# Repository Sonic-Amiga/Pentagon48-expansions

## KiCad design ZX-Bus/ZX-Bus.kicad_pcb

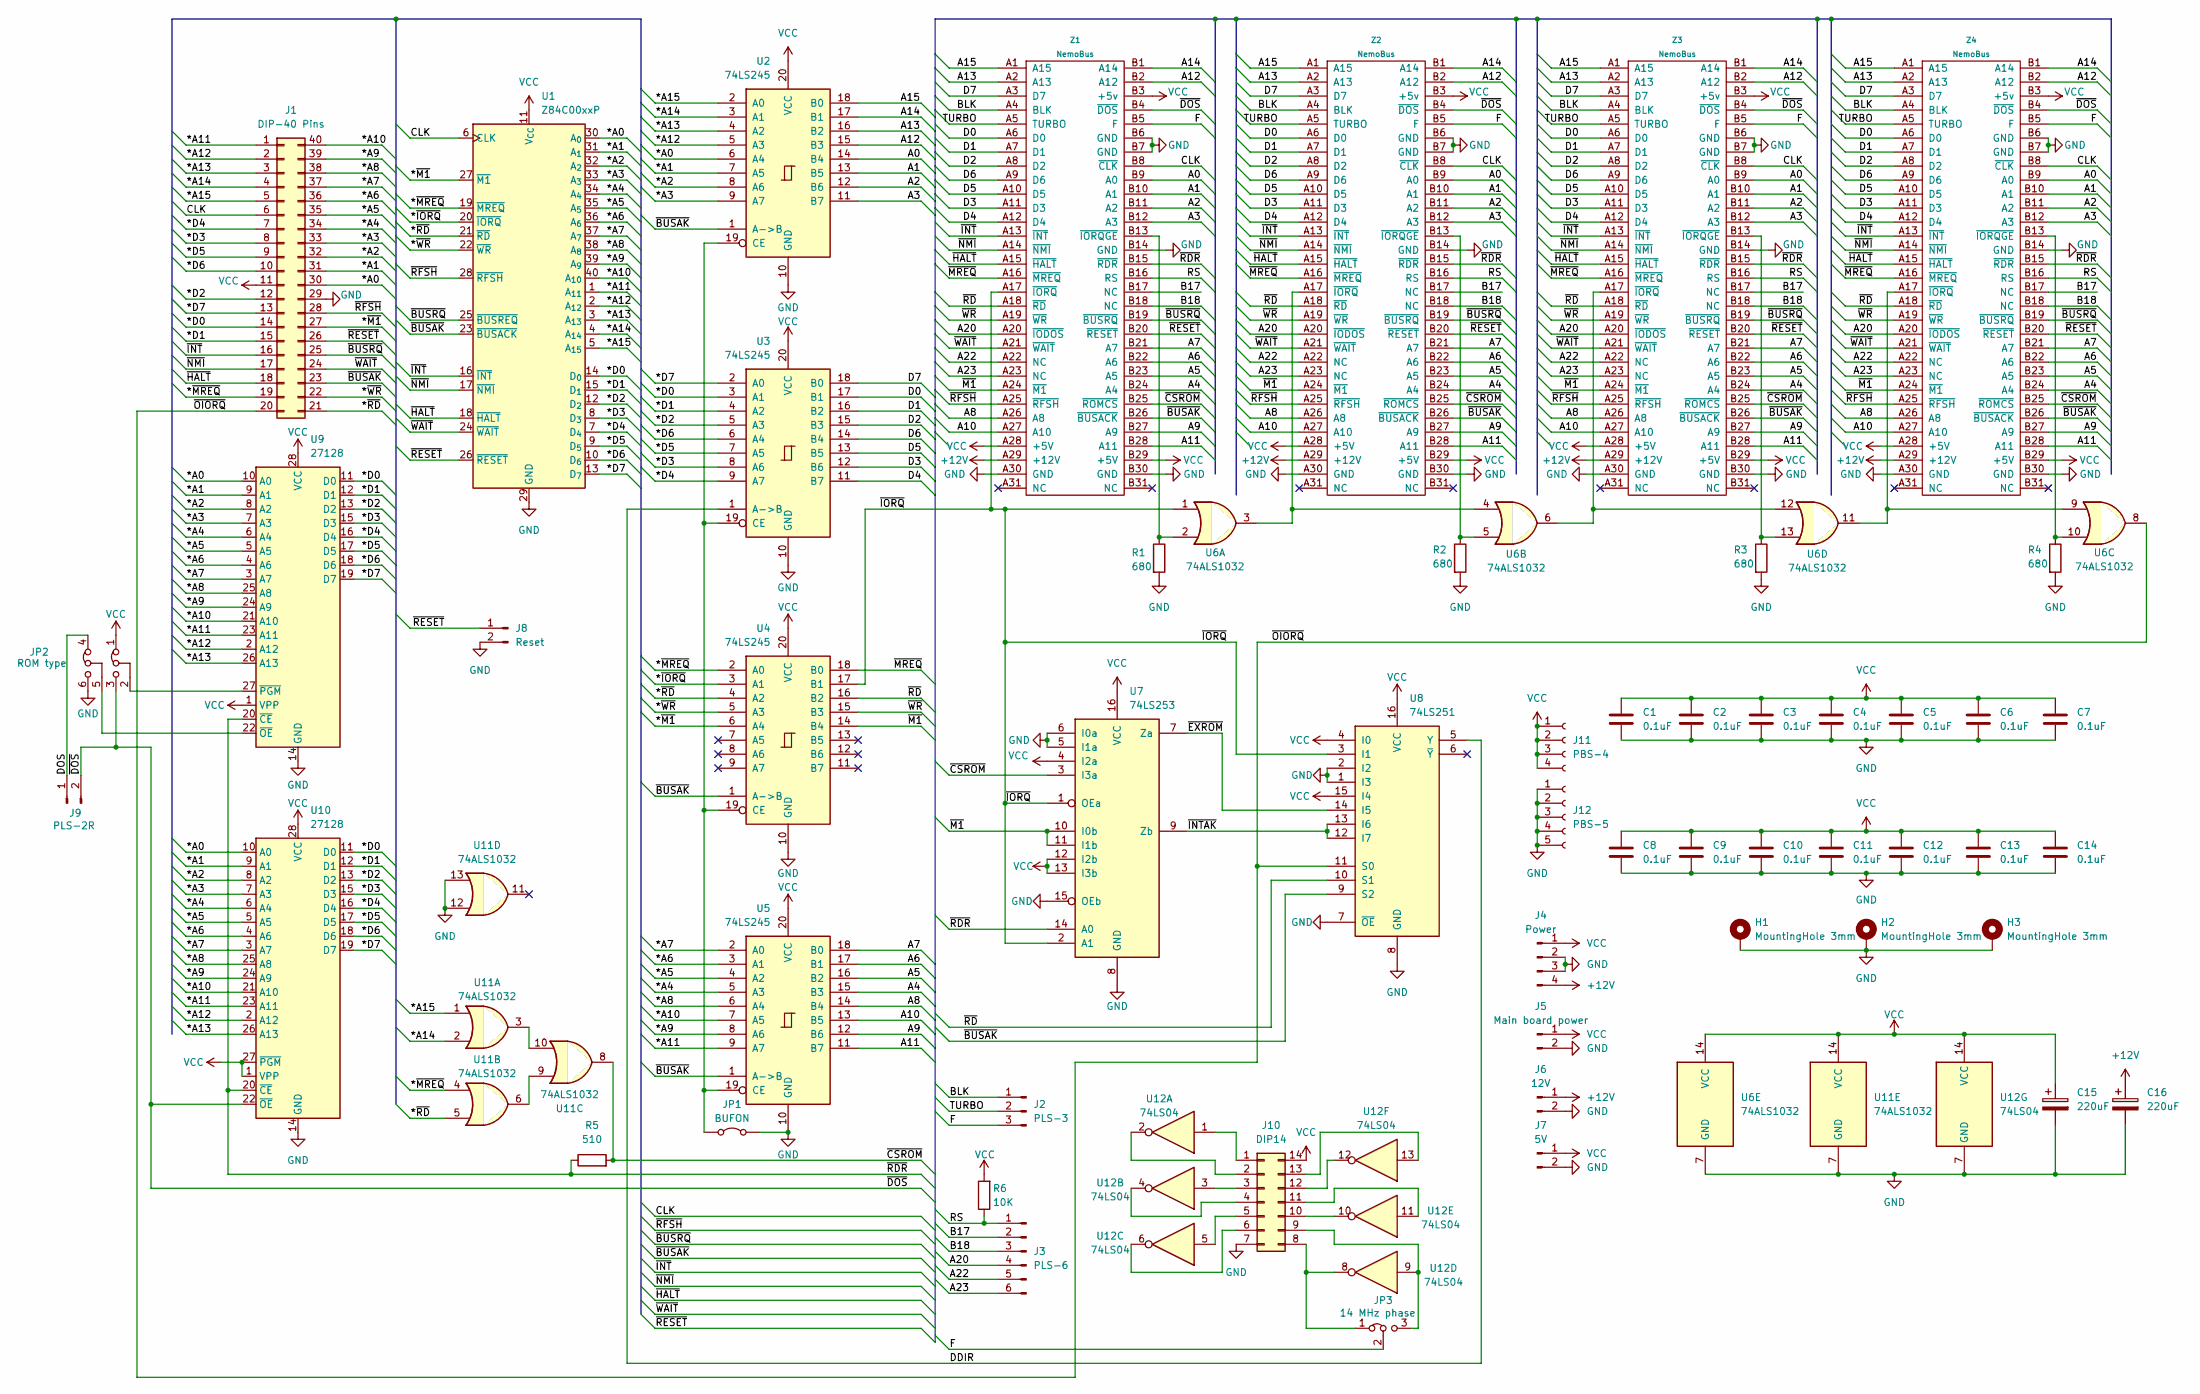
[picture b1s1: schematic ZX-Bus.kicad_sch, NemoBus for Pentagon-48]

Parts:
C1, C2, C3, C4, C5, C6, C7, C8, C9, C10, C11, C12, C13, C14: 0.1uF; C_Disc_D4.3mm_W1.9mm_P5.00mm
C15, C16: 220uF; CP_Radial_D5.0mm_P2.50mm
H1, H2, H3: MountingHole 3mm; MountingHole_3mm_Pad
J1: DIP-40 Pins; DIP40
J2: PLS-3; PinHeader_1x03_P2.54mm_Vertical
J3: PLS-6; PinHeader_1x06_P2.54mm_Vertical
J4: Power; PhoenixContact_MSTBA_2,5_4-G-5,08_1x04_P5.08mm_Horizontal
J5: Main board power; PhoenixContact_MC_1,5_2-G-5.08_1x02_P5.08mm_Horizontal
J6: 12V; JST_XH_S2B-XH-A-1_1x02_P2.50mm_Horizontal
J7: 5V; JST_XH_S2B-XH-A-1_1x02_P2.50mm_Horizontal
J8: Reset; PinHeader_1x02_P2.54mm_Vertical
J9: PLS-2R; PinHeader_1x02_P2.54mm_Horizontal
J10: DIP14; DIP-14_W7.62mm-Pins
J11: PBS-4; PinSocket_1x04_P2.54mm_Vertical
J12: PBS-5; PinSocket_1x05_P2.54mm_Vertical
JP1: BUFON; TestPoint_2Pads_Pitch2.54mm_Drill0.8mm
JP2: ROM type; PinHeader_3x02_P2.54mm_Vertical
JP3: 14 MHz phase; PinHeader_1x03_P2.54mm_Vertical
R1, R2, R3, R4: 680; R_Axial_DIN0207_L6.3mm_D2.5mm_P10.16mm_Horizontal
R5: 510; R_Axial_DIN0207_L6.3mm_D2.5mm_P10.16mm_Horizontal
R6: 10K; R_Axial_DIN0207_L6.3mm_D2.5mm_P10.16mm_Horizontal
U1: Z84C00xxP; DIP-40_W15.24mm_Socket
U2, U3, U4, U5: 74LS245; DIP-20_W7.62mm
U6, U11: 74ALS1032; DIP-14_W7.62mm
U7: 74LS253; DIP-16_W7.62mm
U8: 74LS251; DIP-16_W7.62mm
U9, U10: 27128; DIP-28_W15.24mm_Socket
U12: 74LS04; DIP-14_W7.62mm_Socket
Z1, Z2, Z3, Z4: NemoBus; NemoBus_SL62_Slot

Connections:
+12V: C16.1, J4.4, J6.1, Z1.A29 (+12V), Z2.A29 (+12V), Z3.A29 (+12V), Z4.A29 (+12V)
/*A0: J1.30, U1.30 (A_{0}), U2.6 (A4), U9.10 (A0), U10.10 (A0)
/*A1: J1.31, U1.31 (A_{1}), U2.7 (A5), U9.9 (A1), U10.9 (A1)
/*A2: J1.32, U1.32 (A_{2}), U2.8 (A6), U9.8 (A2), U10.8 (A2)
/*A3: J1.33, U1.33 (A_{3}), U2.9 (A7), U9.7 (A3), U10.7 (A3)
/*A4: J1.34, U1.34 (A_{4}), U5.5 (A3), U9.6 (A4), U10.6 (A4)
/*A5: J1.35, U1.35 (A_{5}), U5.4 (A2), U9.5 (A5), U10.5 (A5)
/*A6: J1.36, U1.36 (A_{6}), U5.3 (A1), U9.4 (A6), U10.4 (A6)
/*A7: J1.37, U1.37 (A_{7}), U5.2 (A0), U9.3 (A7), U10.3 (A7)
/*A8: J1.38, U1.38 (A_{8}), U5.6 (A4), U9.25 (A8), U10.25 (A8)
/*A9: J1.39, U1.39 (A_{9}), U5.8 (A6), U9.24 (A9), U10.24 (A9)
/*A10: J1.40, U1.40 (A_{10}), U5.7 (A5), U9.21 (A10), U10.21 (A10)
/*A11: J1.1, U1.1 (A_{11}), U5.9 (A7), U9.23 (A11), U10.23 (A11)
/*A12: J1.2, U1.2 (A_{12}), U2.5 (A3), U9.2 (A12), U10.2 (A12)
/*A13: J1.3, U1.3 (A_{13}), U2.4 (A2), U9.26 (A13), U10.26 (A13)
/*A14: J1.4, U1.4 (A_{14}), U2.3 (A1), U11.2
/*A15: J1.5, U1.5 (A_{15}), U2.2 (A0), U11.1
/*D0: J1.14, U1.14 (D_{0}), U3.3 (A1), U9.11 (D0), U10.11 (D0)
/*D1: J1.15, U1.15 (D_{1}), U3.4 (A2), U9.12 (D1), U10.12 (D1)
/*D2: J1.12, U1.12 (D_{2}), U3.5 (A3), U9.13 (D2), U10.13 (D2)
/*D3: J1.8, U1.8 (D_{3}), U3.8 (A6), U9.15 (D3), U10.15 (D3)
/*D4: J1.7, U1.7 (D_{4}), U3.9 (A7), U9.16 (D4), U10.16 (D4)
/*D5: J1.9, U1.9 (D_{5}), U3.7 (A5), U9.17 (D5), U10.17 (D5)
/*D6: J1.10, U1.10 (D_{6}), U3.6 (A4), U9.18 (D6), U10.18 (D6)
/*D7: J1.13, U1.13 (D_{7}), U3.2 (A0), U9.19 (D7), U10.19 (D7)
/*~IORQ: U1.20 (~IORQ), U4.3 (A1)
/*~M1: J1.27, U1.27 (~M1), U4.6 (A4)
/*~MREQ: J1.19, U1.19 (~MREQ), U4.2 (A0), U11.4
/*~RD: J1.21, U1.21 (~RD), U4.4 (A2), U11.5
/*~WR: J1.22, U1.22 (~WR), U4.5 (A3)
/A0: U2.14 (B4), Z1.B9 (A0), Z2.B9 (A0), Z3.B9 (A0), Z4.B9 (A0)
/A1: U2.13 (B5), Z1.B10 (A1), Z2.B10 (A1), Z3.B10 (A1), Z4.B10 (A1)
/A2: U2.12 (B6), Z1.B11 (A2), Z2.B11 (A2), Z3.B11 (A2), Z4.B11 (A2)
/A3: U2.11 (B7), Z1.B12 (A3), Z2.B12 (A3), Z3.B12 (A3), Z4.B12 (A3)
/A4: U5.15 (B3), Z1.B24 (A4), Z2.B24 (A4), Z3.B24 (A4), Z4.B24 (A4)
/A5: U5.16 (B2), Z1.B23 (A5), Z2.B23 (A5), Z3.B23 (A5), Z4.B23 (A5)
/A6: U5.17 (B1), Z1.B22 (A6), Z2.B22 (A6), Z3.B22 (A6), Z4.B22 (A6)
/A7: U5.18 (B0), Z1.B21 (A7), Z2.B21 (A7), Z3.B21 (A7), Z4.B21 (A7)
/A8: U5.14 (B4), Z1.A26 (A8), Z2.A26 (A8), Z3.A26 (A8), Z4.A26 (A8)
/A9: U5.12 (B6), Z1.B27 (A9), Z2.B27 (A9), Z3.B27 (A9), Z4.B27 (A9)
/A10: U5.13 (B5), Z1.A27 (A10), Z2.A27 (A10), Z3.A27 (A10), Z4.A27 (A10)
/A11: U5.11 (B7), Z1.B28 (A11), Z2.B28 (A11), Z3.B28 (A11), Z4.B28 (A11)
/A12: U2.15 (B3), Z1.B2 (A12), Z2.B2 (A12), Z3.B2 (A12), Z4.B2 (A12)
/A13: U2.16 (B2), Z1.A2 (A13), Z2.A2 (A13), Z3.A2 (A13), Z4.A2 (A13)
/A14: U2.17 (B1), Z1.B1 (A14), Z2.B1 (A14), Z3.B1 (A14), Z4.B1 (A14)
/A15: U2.18 (B0), Z1.A1 (A15), Z2.A1 (A15), Z3.A1 (A15), Z4.A1 (A15)
/A20: J3.4, Z1.A20 (~IODOS), Z2.A20 (~IODOS), Z3.A20 (~IODOS), Z4.A20 (~IODOS)
/A22: J3.5, Z1.A22 (NC), Z2.A22 (NC), Z3.A22 (NC), Z4.A22 (NC)
/A23: J3.6, Z1.A23 (NC), Z2.A23 (NC), Z3.A23 (NC), Z4.A23 (NC)
/B17: J3.2, Z1.B17 (NC), Z2.B17 (NC), Z3.B17 (NC), Z4.B17 (NC)
/B18: J3.3, Z1.B18 (NC), Z2.B18 (NC), Z3.B18 (NC), Z4.B18 (NC)
/BLK: J2.1, Z1.A4 (BLK), Z2.A4 (BLK), Z3.A4 (BLK), Z4.A4 (BLK)
/CLK: J1.6, U1.6 (CLK), Z1.B8 (~CLK), Z2.B8 (~CLK), Z3.B8 (~CLK), Z4.B8 (~CLK)
/D0: U3.17 (B1), Z1.A6 (D0), Z2.A6 (D0), Z3.A6 (D0), Z4.A6 (D0)
/D1: U3.16 (B2), Z1.A7 (D1), Z2.A7 (D1), Z3.A7 (D1), Z4.A7 (D1)
/D2: U3.15 (B3), Z1.A8 (D2), Z2.A8 (D2), Z3.A8 (D2), Z4.A8 (D2)
/D3: U3.12 (B6), Z1.A11 (D3), Z2.A11 (D3), Z3.A11 (D3), Z4.A11 (D3)
/D4: U3.11 (B7), Z1.A12 (D4), Z2.A12 (D4), Z3.A12 (D4), Z4.A12 (D4)
/D5: U3.13 (B5), Z1.A10 (D5), Z2.A10 (D5), Z3.A10 (D5), Z4.A10 (D5)
/D6: U3.14 (B4), Z1.A9 (D6), Z2.A9 (D6), Z3.A9 (D6), Z4.A9 (D6)
/D7: U3.18 (B0), Z1.A3 (D7), Z2.A3 (D7), Z3.A3 (D7), Z4.A3 (D7)
/DDIR: U3.1 (A->B), U8.5 (Y)
/DOS: J9.1, JP2.4 (A)
/F: J2.3, JP3.2 (C), Z1.B5 (F), Z2.B5 (F), Z3.B5 (F), Z4.B5 (F)
/RS: J3.1, R6.1, Z1.B16 (RS), Z2.B16 (RS), Z3.B16 (RS), Z4.B16 (RS)
/TURBO: J2.2, Z1.A5 (TURBO), Z2.A5 (TURBO), Z3.A5 (TURBO), Z4.A5 (TURBO)
/~BUSAK: J1.23, U1.23 (~BUSACK), U2.1 (A->B), U4.1 (A->B), U5.1 (A->B), U8.9 (S2), Z1.B26 (~BUSACK), Z2.B26 (~BUSACK), Z3.B26 (~BUSACK), Z4.B26 (~BUSACK)
/~BUSRQ: J1.25, U1.25 (~BUSREQ), Z1.B19 (~BUSRQ), Z2.B19 (~BUSRQ), Z3.B19 (~BUSRQ), Z4.B19 (~BUSRQ)
/~CSROM: R5.2, U7.3 (I3a), U11.8, Z1.B25 (~ROMCS), Z2.B25 (~ROMCS), Z3.B25 (~ROMCS), Z4.B25 (~ROMCS)
/~DOS: J9.2, JP2.3 (B), U10.22 (~OE), Z1.B4 (~DOS), Z2.B4 (~DOS), Z3.B4 (~DOS), Z4.B4 (~DOS)
/~EXROM: U7.7 (Za), U8.14 (I5)
/~HALT: J1.18, U1.18 (~HALT), Z1.A15 (~HALT), Z2.A15 (~HALT), Z3.A15 (~HALT), Z4.A15 (~HALT)
/~INTAK: U7.9 (Zb), U8.12 (I7), U8.13 (I6)
/~INT: J1.16, U1.16 (~INT), Z1.A13 (~INT), Z2.A13 (~INT), Z3.A13 (~INT), Z4.A13 (~INT)
/~IORQ: U4.17 (B1), U6.1, U7.1 (OEa), U7.2 (A1), U8.3 (I1), Z1.A17 (~IORQ)
/~M1: U4.14 (B4), U7.10 (I0b), U7.11 (I1b), Z1.A24 (~M1), Z2.A24 (~M1), Z3.A24 (~M1), Z4.A24 (~M1)
/~MREQ: U4.18 (B0), Z1.A16 (~MREQ), Z2.A16 (~MREQ), Z3.A16 (~MREQ), Z4.A16 (~MREQ)
/~NMI: J1.17, U1.17 (~NMI), Z1.A14 (~NMI), Z2.A14 (~NMI), Z3.A14 (~NMI), Z4.A14 (~NMI)
/~OIORQ: J1.20, U6.8, U8.11 (S0)
/~RDR: R5.1, U7.14 (A0), U9.20 (~CE), U10.20 (~CE), Z1.B15 (~RDR), Z2.B15 (~RDR), Z3.B15 (~RDR), Z4.B15 (~RDR)
/~RD: U4.16 (B2), U8.10 (S1), Z1.A18 (~RD), Z2.A18 (~RD), Z3.A18 (~RD), Z4.A18 (~RD)
/~RESET: J1.26, J8.1, U1.26 (~RESET), Z1.B20 (~RESET), Z2.B20 (~RESET), Z3.B20 (~RESET), Z4.B20 (~RESET)
/~RFSH: J1.28, U1.28 (~RFSH), Z1.A25 (~RFSH), Z2.A25 (~RFSH), Z3.A25 (~RFSH), Z4.A25 (~RFSH)
/~WAIT: J1.24, U1.24 (~WAIT), Z1.A21 (~WAIT), Z2.A21 (~WAIT), Z3.A21 (~WAIT), Z4.A21 (~WAIT)
/~WR: U4.15 (B3), Z1.A19 (~WR), Z2.A19 (~WR), Z3.A19 (~WR), Z4.A19 (~WR)
GND: C1.2, C2.2, C3.2, C4.2, C5.2, C6.2, C7.2, C8.2, C9.2, C10.2, C11.2, C12.2, C13.2, C14.2, C15.2, C16.2, H1.1 (1_1), H2.1 (1_1), H3.1 (1_1), J1.29, J4.2, J4.3, J5.2, J6.2, J7.2, J8.2, J10.7, J12.1, J12.2, J12.3, J12.4, J12.5, JP1.2 (B), JP2.6 (B), R1.2, R2.2, R3.2, R4.2, U1.29 (GND), U2.10 (GND), U3.10 (GND), U4.10 (GND), U5.10 (GND), U6.7 (GND), U7.5 (I1a), U7.6 (I0a), U7.8 (GND), U7.15 (OEb), U8.1 (I3), U8.2 (I2), U8.7 (~OE), U8.8 (GND), U9.14 (GND), U10.14 (GND), U11.7 (GND), U11.12, U11.13, U12.7 (GND), Z1.A30 (GND), Z1.B6 (GND), Z1.B7 (GND), Z1.B14 (GND), Z1.B30 (GND), Z2.A30 (GND), Z2.B6 (GND), Z2.B7 (GND), Z2.B14 (GND), Z2.B30 (GND), Z3.A30 (GND), Z3.B6 (GND), Z3.B7 (GND), Z3.B14 (GND), Z3.B30 (GND), Z4.A30 (GND), Z4.B6 (GND), Z4.B7 (GND), Z4.B14 (GND), Z4.B30 (GND)
unnamed: J10.1, U12.1
unnamed: J10.2, U12.2
unnamed: J10.3, U12.3
unnamed: J10.4, U12.4
unnamed: J10.5, U12.5
unnamed: J10.6, U12.6
unnamed: J10.8, JP3.1 (A), U12.8
unnamed: J10.9, JP3.3 (B), U12.9
unnamed: J10.10, U12.10
unnamed: J10.11, U12.11
unnamed: J10.12, U12.12
unnamed: J10.13, U12.13
unnamed: JP1.1 (A), U2.19 (CE), U3.19 (CE), U4.19 (CE), U5.19 (CE)
unnamed: JP2.5 (C), U9.22 (~OE)
unnamed: JP2.2 (C), U9.27 (~PGM)
unnamed: U11.6, U11.9
unnamed: U11.3, U11.10
unnamed: R1.1, U6.2, Z1.B13 (~IORQGE)
unnamed: R2.1, U6.5, Z2.B13 (~IORQGE)
unnamed: U6.3, U6.4, Z2.A17 (~IORQ)
unnamed: R3.1, U6.13, Z3.B13 (~IORQGE)
unnamed: U6.6, U6.12, Z3.A17 (~IORQ)
unnamed: R4.1, U6.10, Z4.B13 (~IORQGE)
unnamed: U6.9, U6.11, Z4.A17 (~IORQ)
VCC: C1.1, C2.1, C3.1, C4.1, C5.1, C6.1, C7.1, C8.1, C9.1, C10.1, C11.1, C12.1, C13.1, C14.1, C15.1, J1.11, J4.1, J5.1, J7.1, J10.14, J11.1, J11.2, J11.3, J11.4, JP2.1 (A), R6.2, U1.11 (V_{CC}), U2.20 (VCC), U3.20 (VCC), U4.20 (VCC), U5.20 (VCC), U6.14 (VCC), U7.4 (I2a), U7.12 (I2b), U7.13 (I3b), U7.16 (VCC), U8.4 (I0), U8.15 (I4), U8.16 (VCC), U9.1 (VPP), U9.28 (VCC), U10.1 (VPP), U10.27 (~PGM), U10.28 (VCC), U11.14 (VCC), U12.14 (VCC), Z1.A28 (+5V), Z1.B3 (+5v), Z1.B29 (+5V), Z2.A28 (+5V), Z2.B3 (+5v), Z2.B29 (+5V), Z3.A28 (+5V), Z3.B3 (+5v), Z3.B29 (+5V), Z4.A28 (+5V), Z4.B3 (+5v), Z4.B29 (+5V)

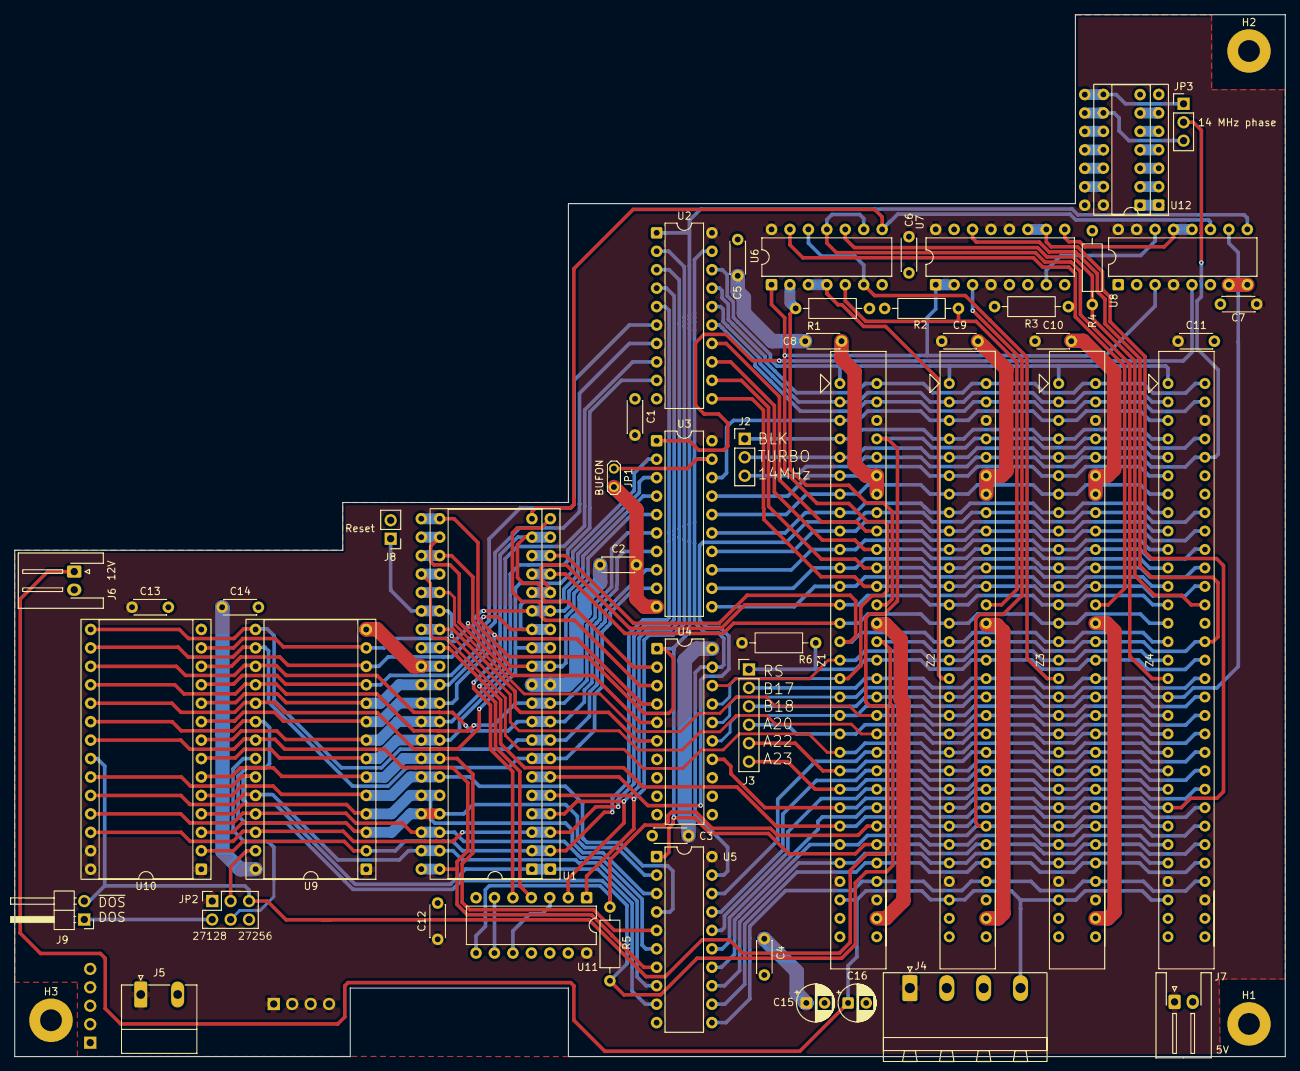
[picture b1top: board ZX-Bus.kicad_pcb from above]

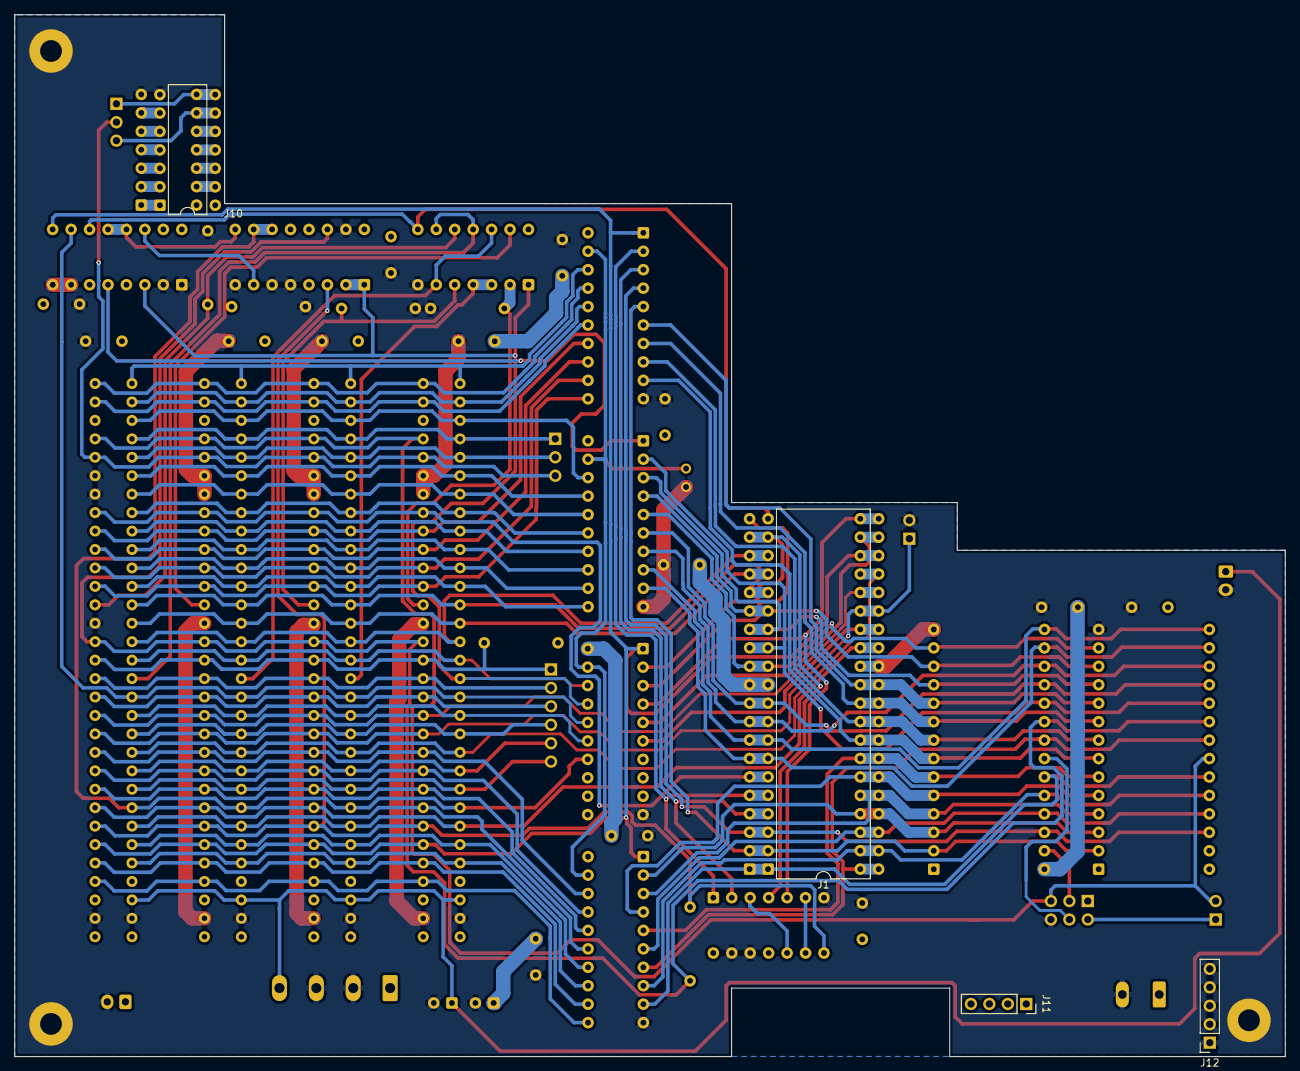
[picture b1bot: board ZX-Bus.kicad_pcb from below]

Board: 2 copper layers, 175.0 x 143.5 mm, 56 parts (2 on the bottom side), 111 nets.

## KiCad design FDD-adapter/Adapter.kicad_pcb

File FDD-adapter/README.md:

# Введение

Этот проект представляет собой переходник на стандартный интерфейс флоппи-дисковода
для ZX-Spectrum-совместимого компьютера "Пентагон-48". Для классических вариантов
платы, не имеющих буферизации линий выбора дисковода, предусмотрена возможность
установки буфера 74LS07. Если у вас есть этот буфер на плате, вы можете просто
замкнуть накоротко соответствующие дорожки.

# Рекомендации по сборке и подключению

Данный переходник использует 30-контактный разъём со стороны Пентагона, хотя на плате
компьютера посадочное место под разъём 32 контакта. Это сделано по двум соображениям.
Во-первых, стандартные разъёмы IDC имеются только под 30 контактов. Во-вторых, подача
питания через разъём дисковода на весь компьютер - не очень хорошая идея из-за тонких
дорожек. Поэтому я принял решение использовать 30-контактный разъём для данных и
отдельный 2-контактный разъём для подачи питания 12В. В качестве последнего хорошо
подходит разъём JST EHR-2

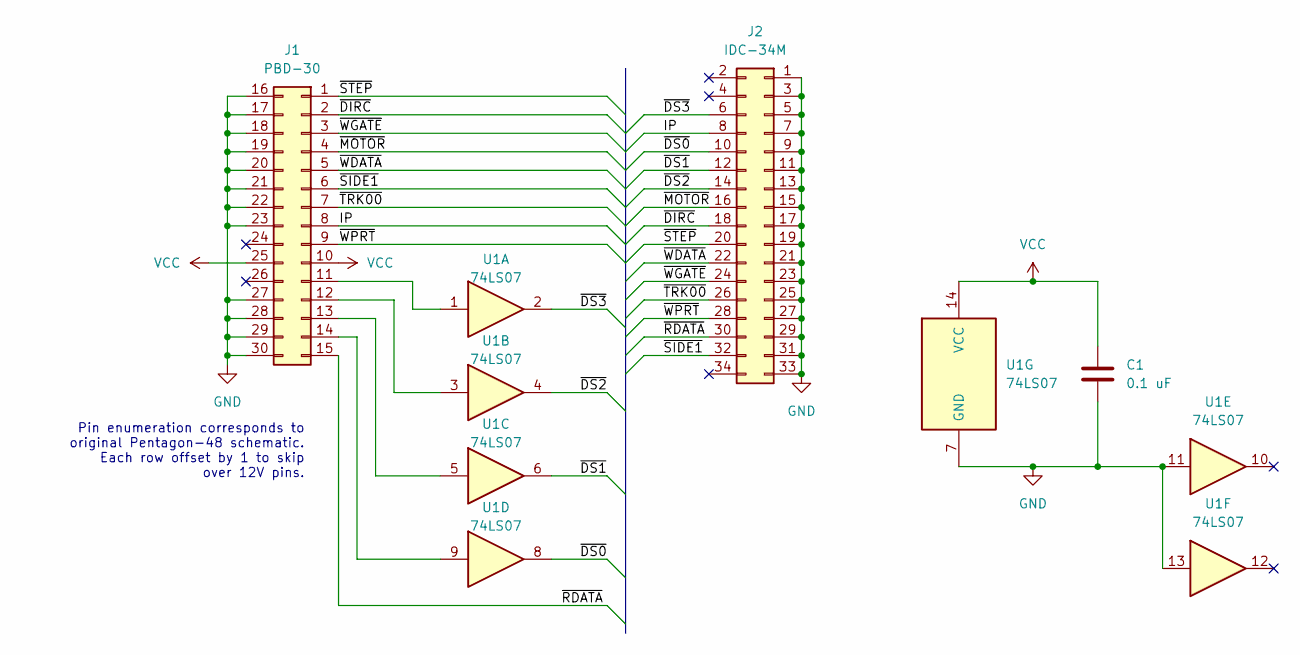
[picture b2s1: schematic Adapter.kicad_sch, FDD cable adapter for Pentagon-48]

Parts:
C1: 0.1 uF; C_0805_2012Metric_Pad1.18x1.45mm_HandSolder
J1: PBD-30; PinSocket_2x16_P2.54mm_EdgeMounted
J2: IDC-34M; IDC-Header_2x17_P2.54mm_Vertical
U1: 74LS07; SOIC-14_3.9x8.7mm_P1.27mm

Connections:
/IP: J1.8, J2.8
/~DIRC: J1.2, J2.18
/~DS0: J2.10, U1.8
/~DS1: J2.12, U1.6
/~DS2: J2.14, U1.4
/~DS3: J2.6, U1.2
/~MOTOR: J1.4, J2.16
/~RDATA: J1.15, J2.30
/~SIDE1: J1.6, J2.32
/~STEP: J1.1, J2.20
/~TRK00: J1.7, J2.26
/~WDATA: J1.5, J2.22
/~WGATE: J1.3, J2.24
/~WPRT: J1.9, J2.28
GND: C1.2, J1.16, J1.17, J1.18, J1.19, J1.20, J1.21, J1.22, J1.23, J1.27, J1.28, J1.29, J1.30, J2.1, J2.3, J2.5, J2.7, J2.9, J2.11, J2.13, J2.15, J2.17, J2.19, J2.21, J2.23, J2.25, J2.27, J2.29, J2.31, J2.33, U1.7 (GND), U1.11, U1.13
unnamed: J1.11, U1.1
unnamed: J1.12, U1.3
unnamed: J1.13, U1.5
unnamed: J1.14, U1.9
VCC: C1.1, J1.10, J1.25, U1.14 (VCC)

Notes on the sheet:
Pin enumeration corresponds to original Pentagon-48 schematic. Each row offset by 1 to skip over 12V pins.

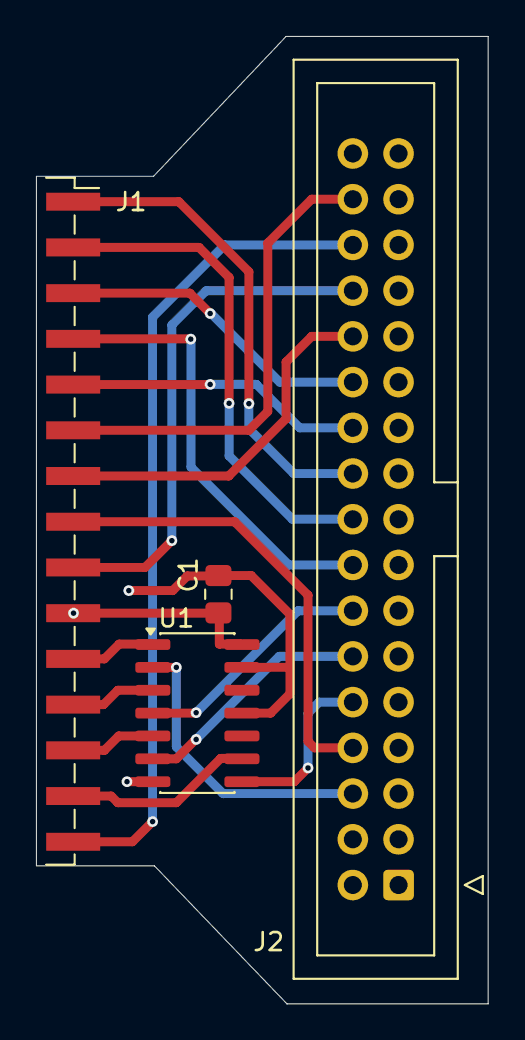
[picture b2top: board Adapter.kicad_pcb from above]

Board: 2 copper layers, 25.1 x 53.7 mm, 4 parts (0 on the bottom side), 20 nets.

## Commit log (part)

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2026-04-28 Add FDD-adapter
    An adapter from Pentagon48-specific to a standard 34-pin floppy drive connector
2026-04-28 FDD-adapter: Add documentation
    Simple README (in russian), schematic in PDF and picture of assembled product.
2026-04-28 FDD-adapter: Fix image
    Typo in README
2026-05-15 ZX-Bus
    NemoBus for Pentagon-48. Work in progress.
2026-05-15 ZX-Bus: Flip slots on the schematic
    This is actually original orientation, during schematic creation i flipped them
    for historical reason. It's easier to compare with other versions.
2026-05-16 ZX-Bus: Proper sides on NemoBus slots
    Fix swapped A and B rows
2026-05-24 ZX-Bus: Complete v1
    Add missing parts and complete layout
2026-06-06 ZX-Bus: Some corrections
    Corrected size and layout after verification. SL-62 footprints with proper
    courtyards.
2026-06-06 ZX-Bus: More layout improvements
    Some ideas
2026-06-08 ZX-Bus: Fix holes position and borders
    According to measurements and fit test with the mockup
2026-06-08 ZX-Bus: Fix ROM type select jumper
    We actually need to switch two lines.
2026-06-14 ZX-Bus: More taps
    Add 14MHz tap to U2 (on main board). Add some more power headers so that we are
    able to connect the board with no need to solder more power cables. It's
    possible to drill the main board in those places and install power pins.
2026-06-14 ZX-Bus: Fix 3D visualization
    Add pins to IC connector footprints
2026-06-15 ZX-Bus: Correct mounting hole placement
    Based on mockup testing and re-measurement
2026-06-17 ZX-Bus: Adjust +5V connector position
    Move by 0.5mm for easier soldering
2026-06-17 ZX-Bus: Produce gerber
    First revision complete, generate gerbers.
